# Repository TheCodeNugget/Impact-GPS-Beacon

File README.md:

# Impact-GPS-Beacon
Impact activated GPS beacon powered by TI-MSP430 family

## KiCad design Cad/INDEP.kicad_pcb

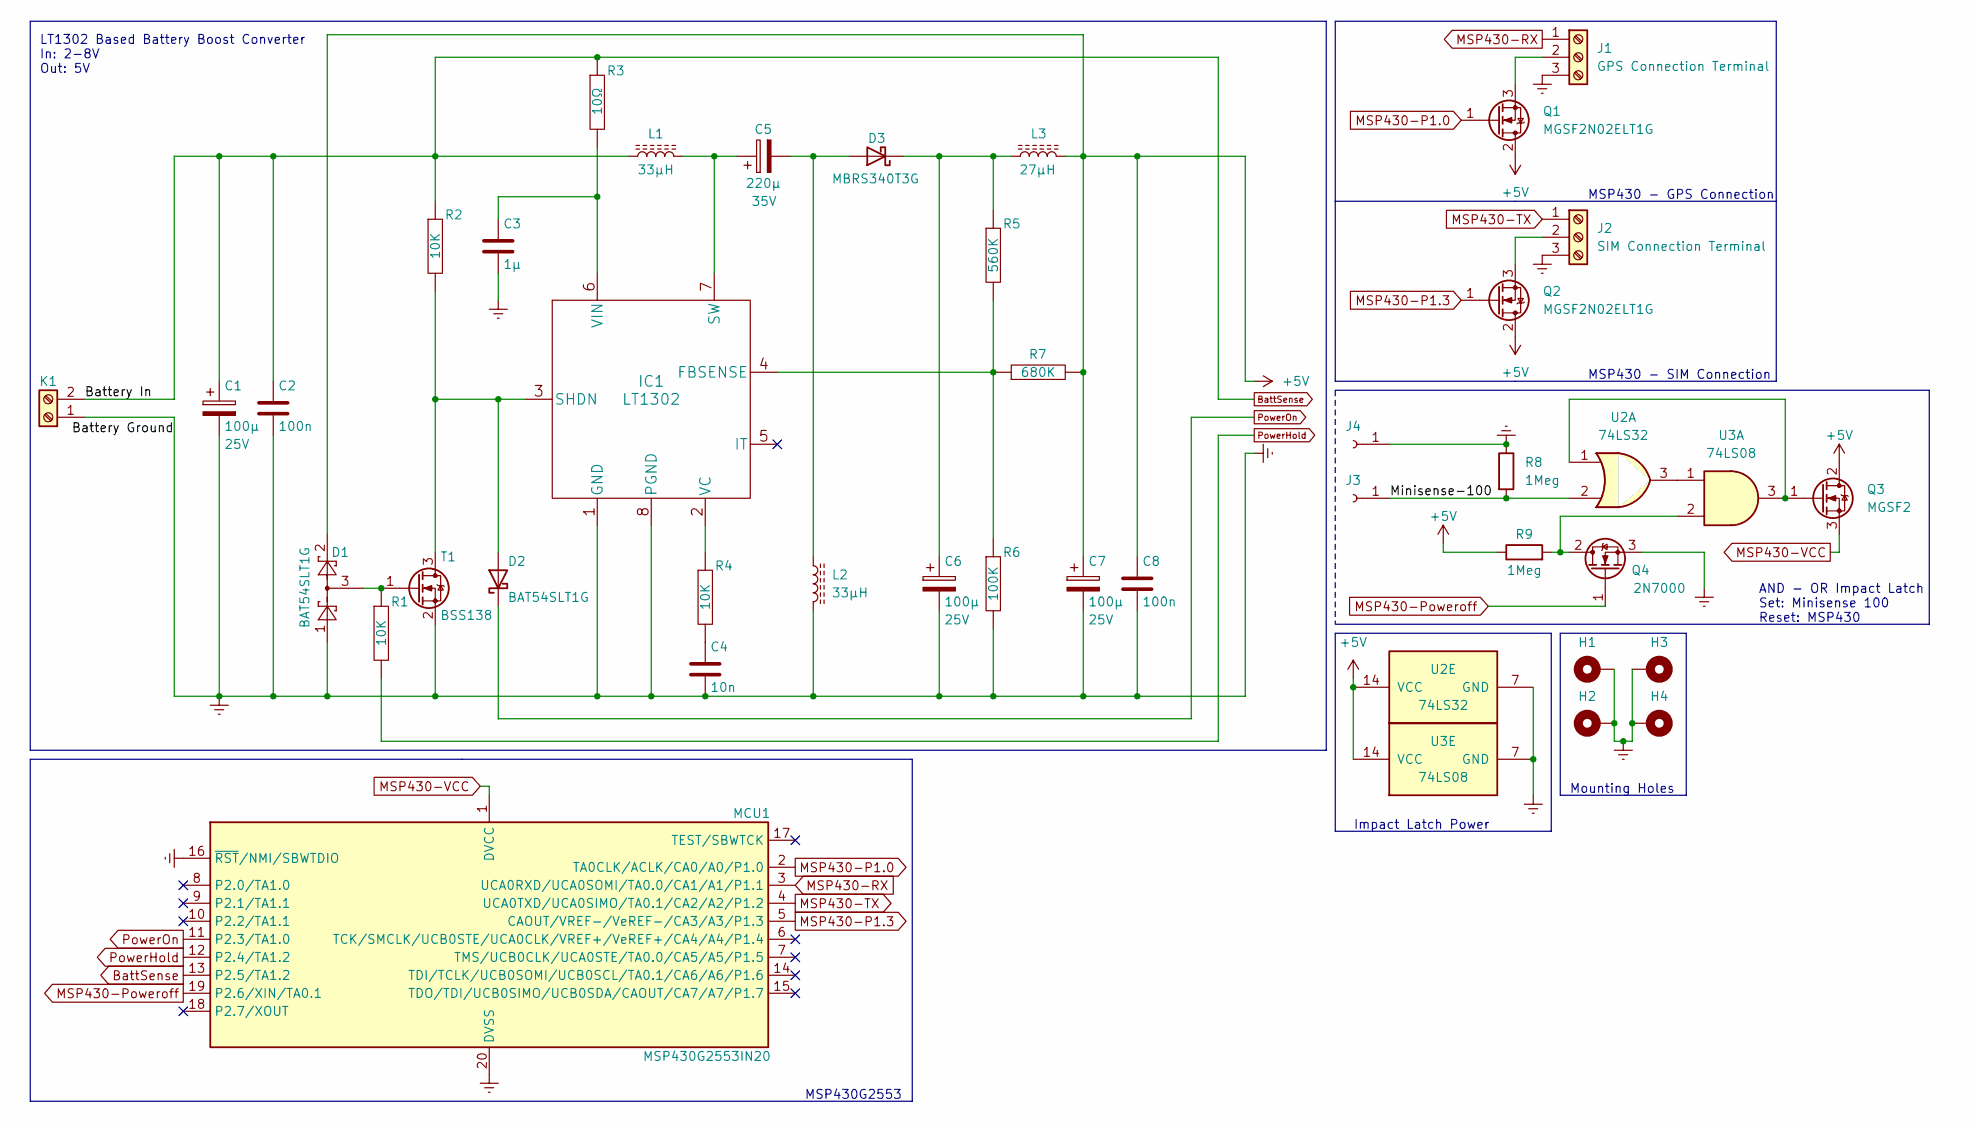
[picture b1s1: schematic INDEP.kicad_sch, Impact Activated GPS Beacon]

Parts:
C1, C6, C7: 100μ; C_1206_3216Metric
C2, C8: 100n; C_0603_1608Metric
C3: 1μ; C_0603_1608Metric
C4: 10n; C_0603_1608Metric
C5: 220μ; C_1206_3216Metric
D1, D2: BAT54SLT1G; SOT-23
D3: MBRS340T3G; D_SMC-RM10_Universal_Handsoldering
H1, H2, H3, H4: MountingHole_Pad; MountingHole_4.3mm_M4_Pad_Via
IC1: LT1302; DIP-8_W7.62mm
J1: GPS Connection Terminal; TerminalBlock_Phoenix_MKDS-1,5-3-5.08_1x03_P5.08mm_Horizont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
J2: SIM Connection Terminal; TerminalBlock_Phoenix_MKDS-1,5-3-5.08_1x03_P5.08mm_Horizont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
J3, J4: Minisense-100 Ground; Pin_D0.7mm_L6.5mm_W1.8mm_FlatFork
K1: Battery Terminal; TerminalBlock_Phoenix_MKDS-1,5-2_1x02_P5.00mm_Horizontal
L1, L2: 33μH; L_1812_4532Metric
L3: 27μH; L_1210_3225Metric
MCU1: MSP430G2553IN20; DIP-20_W7.62mm
Q1, Q2: MGSF2N02ELT1G; SOT-23
Q3: MGSF2; SOT-23
Q4: 2N7000; SOT-23
R1, R2, R4: 10K; R_0603_1608Metric
R3: 10Ω; R_0603_1608Metric
R5: 560K; R_0603_1608Metric
R6: 100K; R_0603_1608Metric
R7: 680K; R_0603_1608Metric
R8, R9: 1Meg; R_0603_1608Metric
T1: BSS138; SOT-23
U2: 74LS32; DIP-14_W7.62mm
U3: 74LS08; DIP-14_W7.62mm

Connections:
+5V: C7.1, C8.1, D1.2, L3.2, Q1.2 (D), Q2.2 (D), Q3.2 (D), R7.2, R9.1, U2.14 (VCC), U3.14 (VCC)
/Minisense-100: J3.1, R8.2, U2.2
BattSense: C1.1, C2.1, K1.2, L1.1, MCU1.13 (P2.5/TA1.2), R2.1, R3.1
Earth: C1.2, C2.2, C3.2, C4.2, C6.2, C7.2, C8.2, D1.1, H1.1, H2.1, H3.1, H4.1, IC1.1 (GND), IC1.8 (PGND), J1.3, J2.3, J4.1, K1.1, L2.2, MCU1.16 (~RST/NMI/SBWTDIO), MCU1.20 (DVSS), Q4.3 (S), R6.2, R8.1, T1.2 (S), U2.7 (GND), U3.7 (GND)
MSP430-P1.0: MCU1.2 (TA0CLK/ACLK/CA0/A0/P1.0), Q1.1 (G)
MSP430-P1.3: MCU1.5 (CAOUT/VREF-/VeREF-/CA3/A3/P1.3), Q2.1 (G)
MSP430-Poweroff: MCU1.19 (P2.6/XIN/TA0.1), Q4.1 (G)
MSP430-RX: J1.1, MCU1.3 (UCA0RXD/UCA0SOMI/TA0.0/CA1/A1/P1.1)
MSP430-TX: J2.1, MCU1.4 (UCA0TXD/UCA0SIMO/TA0.1/CA2/A2/P1.2)
MSP430-VCC: MCU1.1 (DVCC), Q3.3 (S)
unnamed: C3.1, IC1.6 (VIN), R3.2
unnamed: C4.1, R4.2
unnamed: C5.1, IC1.7 (SW), L1.2
unnamed: C5.2, D3.2 (A), L2.1
unnamed: C6.1, D3.1 (K), L3.1, R5.1
unnamed: D1.3, R1.1, T1.1 (G)
unnamed: D2.2 (A), IC1.3 (SHDN), R2.2, T1.3 (D)
unnamed: IC1.2 (VC), R4.1
unnamed: IC1.4 (FBSENSE), R5.2, R6.1, R7.1
unnamed: J1.2, Q1.3 (S)
unnamed: J2.2, Q2.3 (S)
unnamed: Q3.1 (G), U2.1, U3.3
unnamed: Q4.2 (D), R9.2, U3.2
unnamed: U2.3, U3.1
PowerHold: MCU1.12 (P2.4/TA1.2), R1.2
PowerOn: D2.1 (K), MCU1.11 (P2.3/TA1.0)

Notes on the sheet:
LT1302 Based Battery Boost Converter In: 2-8V Out: 5V
MSP430 - GPS Connection
MSP430G2553
AND - OR Impact Latch Set: Minisense 100 Reset: MSP430
Impact Latch Power
Mounting Holes
MSP430 - SIM Connection

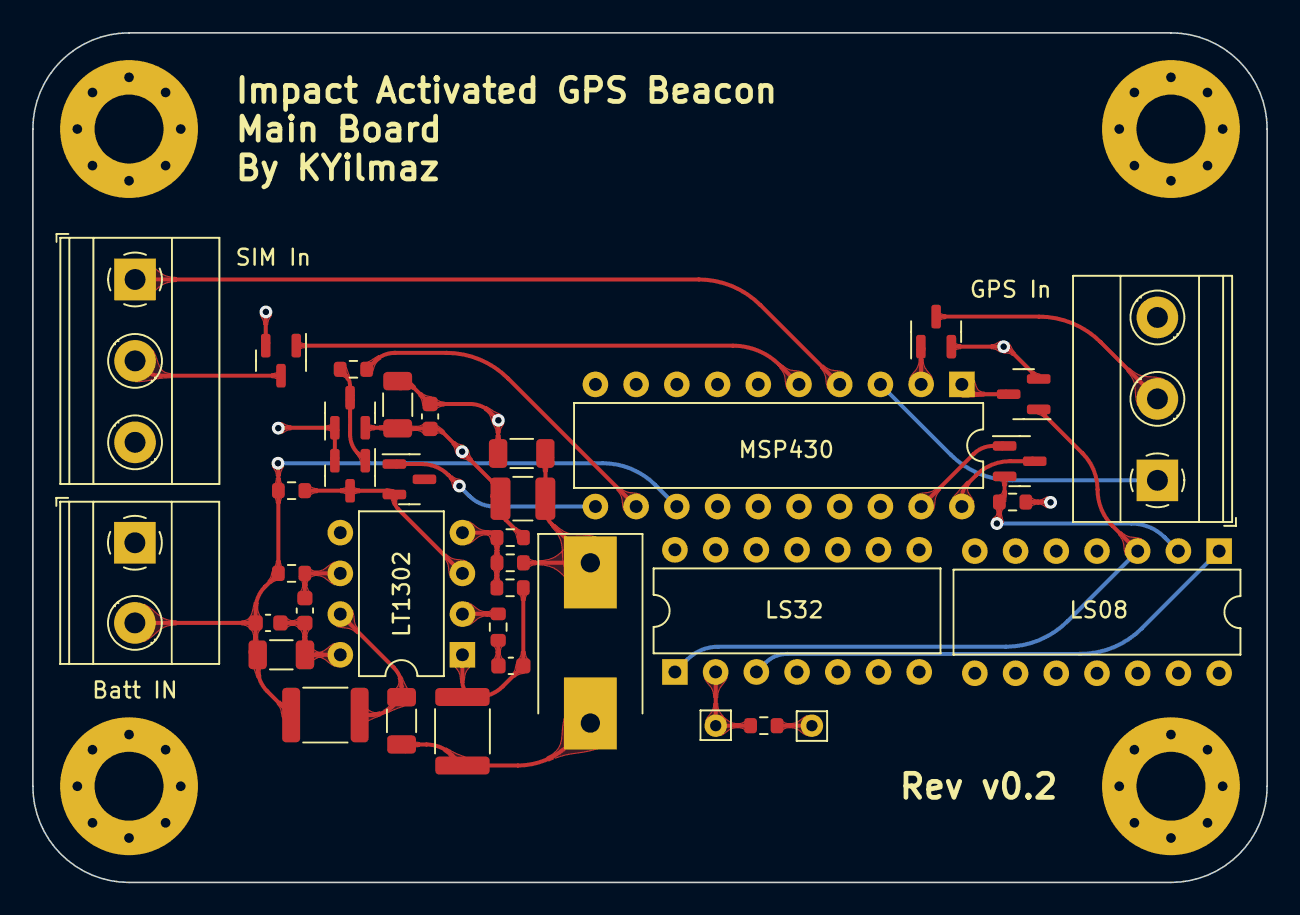
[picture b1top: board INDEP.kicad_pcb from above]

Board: 4 copper layers, 77.0 x 53.0 mm, 41 parts (0 on the bottom side), 26 nets.

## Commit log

2023-04-27 Docs: Docs migrated to repo
2023-04-27 Chore: CAD files migrated to repo
2023-04-27 Docs: Migrated docs to repo
